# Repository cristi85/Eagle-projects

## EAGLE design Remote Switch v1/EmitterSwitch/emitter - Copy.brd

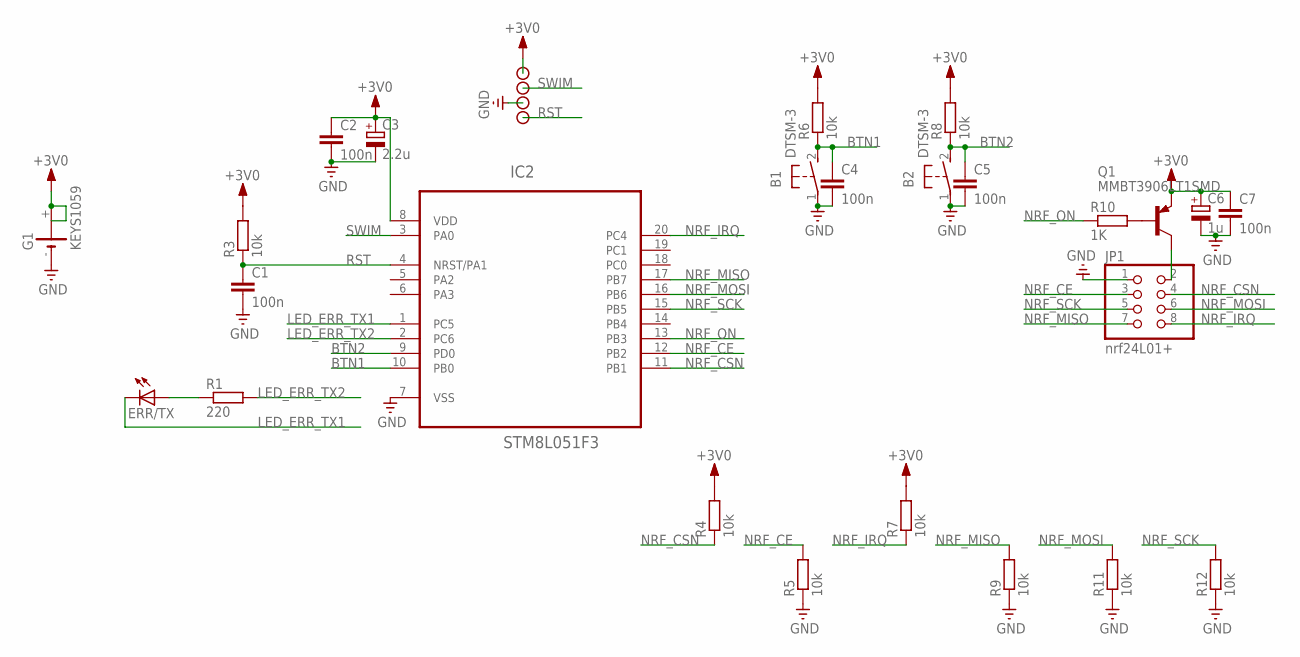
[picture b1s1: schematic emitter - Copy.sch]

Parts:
B1, B2: DTSM-3
C1, C2, C4, C5, C7: 100n; C0603K
C3: 2.2u; SMC_A
C6: 1u; SMC_A
ERR/TX: LED3MM
G1: KEYS1059
IC2: STM8L051F3; TSSOP20
JP1: nrf24L01+; 2X04
Q1: MMBT3906LT1SMD; SOT23-BEC
R1: 220; R0603
R3, R4, R5, R6, R7, R8, R9, R11, R12: 10k; R0603
R10: 1K; R0603
SIG_+3V1: CON_PAD; SMD_PAD
SIG_GND: CON_PAD; SMD_PAD
SIG_RST: CON_PAD; SMD_PAD
SIG_SWIM: CON_PAD; SMD_PAD

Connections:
+3V0: C2.1, C3.+, C6.+, C7.1, G1.+, G1.@+ (+), IC2.8 (VDD), Q1.E, R3.2, R4.2, R6.2, R7.2, R8.2, SIG_+3V1.P$1
BTN1: B1.2, C4.1, IC2.10 (PB0), R6.1
BTN2: B2.2, C5.1, IC2.9 (PD0), R8.1
GND: B1.1, B2.1, C1.2, C2.2, C3.-, C4.2, C5.2, C6.-, C7.2, G1.-, IC2.7 (VSS), JP1.1, R5.1, R9.1, R11.1, R12.1, SIG_GND.P$1
LED_ERR_TX1: ERR/TX.K (C), IC2.1 (PC5)
LED_ERR_TX2: IC2.2 (PC6), R1.2
unnamed: ERR/TX.A, R1.1
unnamed: JP1.2, Q1.C
unnamed: Q1.B, R10.2
NRF_CE: IC2.12 (PB2), JP1.3, R5.2
NRF_CSN: IC2.11 (PB1), JP1.4, R4.1
NRF_IRQ: IC2.20 (PC4), JP1.8, R7.1
NRF_MISO: IC2.17 (PB7), JP1.7, R9.2
NRF_MOSI: IC2.16 (PB6), JP1.6, R11.2
NRF_ON: IC2.13 (PB3), R10.1
NRF_SCK: IC2.15 (PB5), JP1.5, R12.2
RST: C1.1, IC2.4 (NRST/PA1), R3.1, SIG_RST.P$1
SWIM: IC2.3 (PA0), SIG_SWIM.P$1

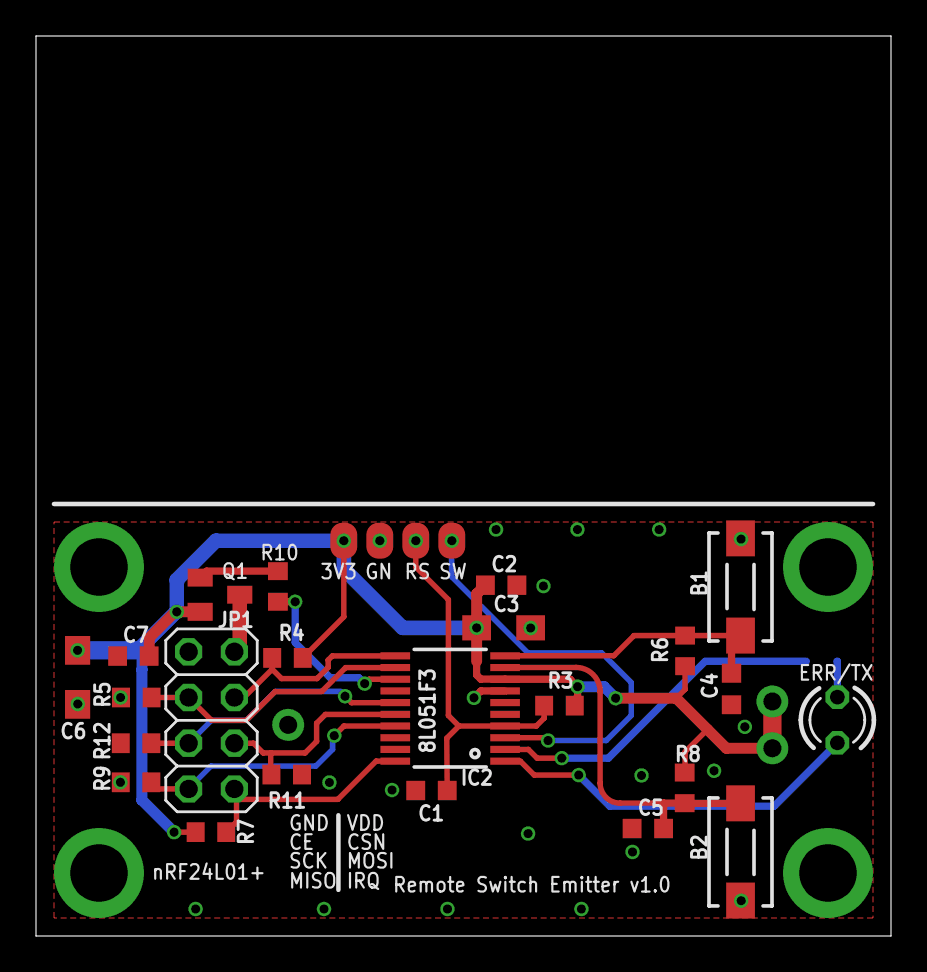
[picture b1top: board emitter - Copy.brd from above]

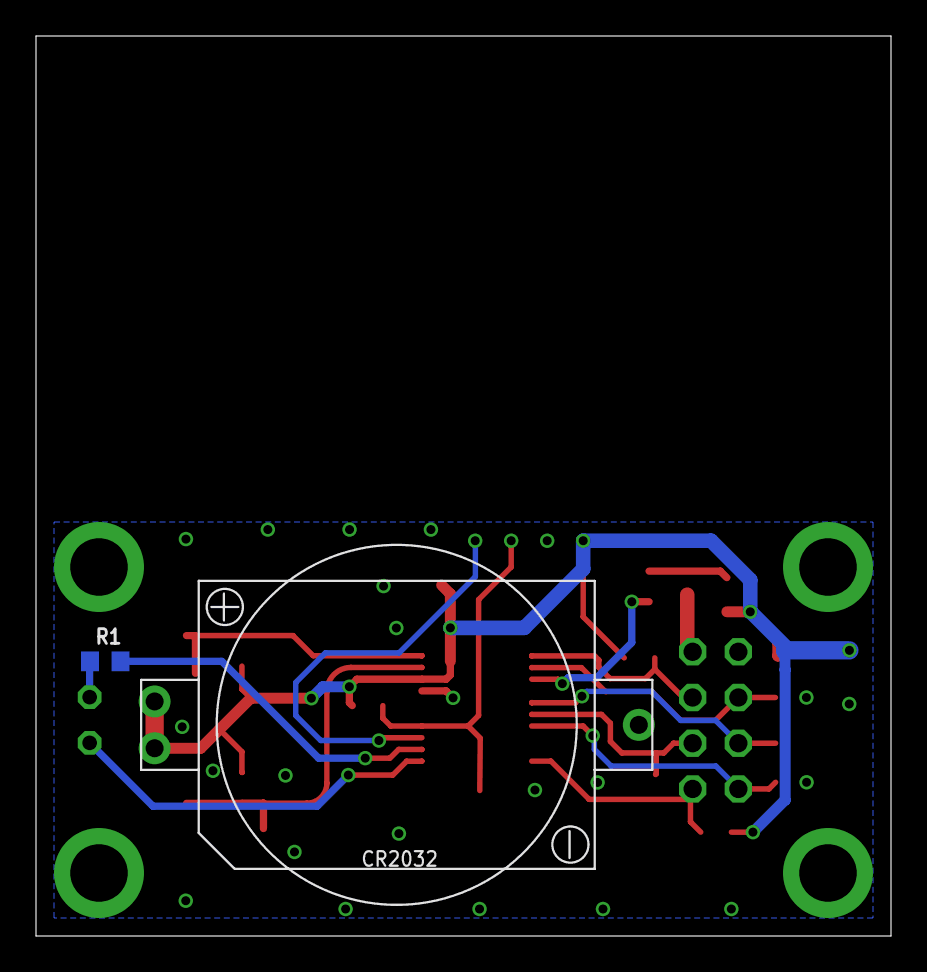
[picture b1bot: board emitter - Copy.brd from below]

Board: 2 copper layers, 47.5 x 50.0 mm, 29 parts (2 on the bottom side), 18 nets.

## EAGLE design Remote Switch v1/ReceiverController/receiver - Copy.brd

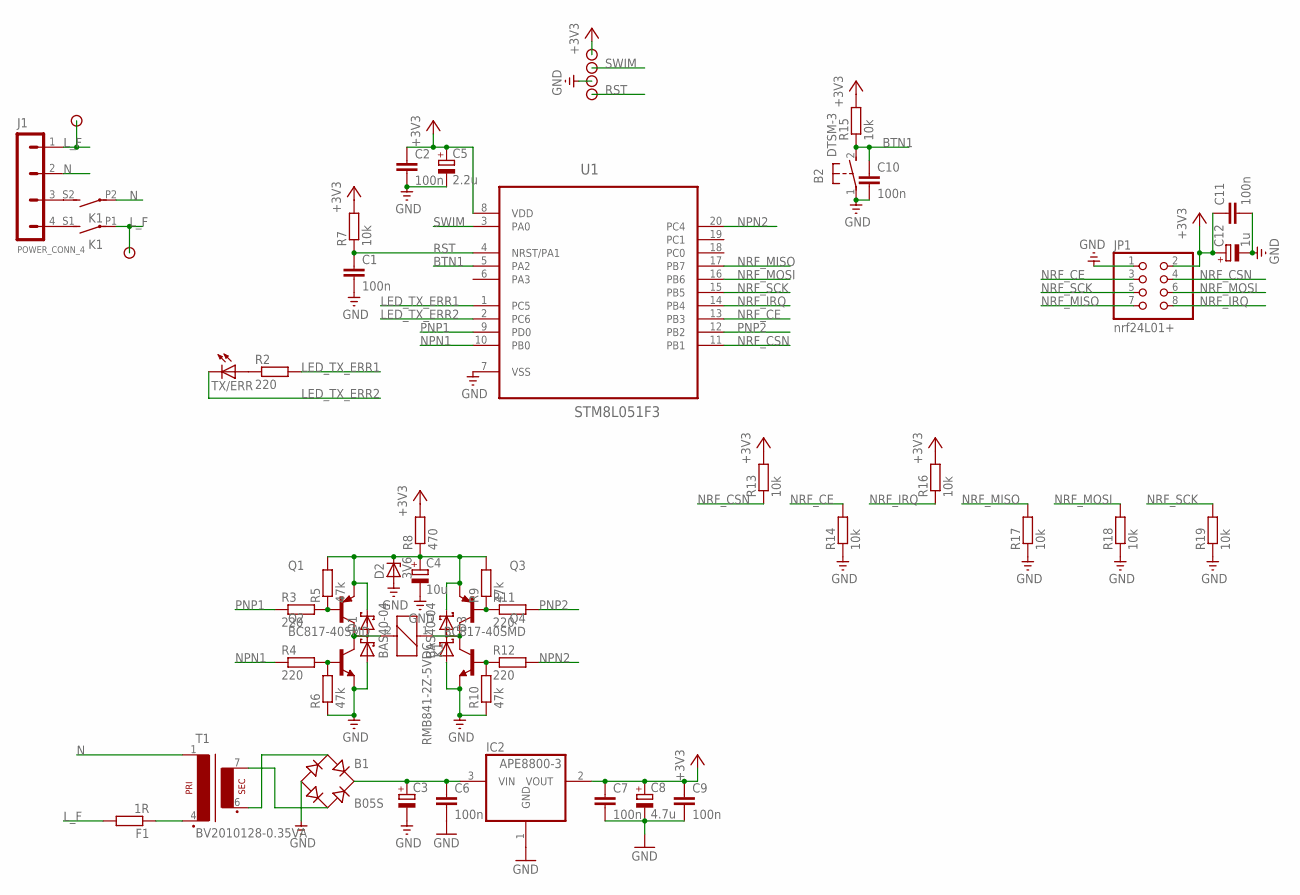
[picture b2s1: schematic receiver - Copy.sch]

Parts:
B1: B05S; MBS
B2: DTSM-3
C1, C2, C6, C7, C9, C10, C11: 100n; C0603K
C3: CPOL-EUSMCB; SMC_B
C4: 10u; SMC_B
C5: 2.2u; SMC_A
C8: 4.7u; SMC_A
C12: 1u; SMC_A
D1, D3: BAS40-04; SOT23
D2: 3V6; SOT23
F1: 1R; 0207/10
IC2: APE8800-3; SOT23
J1: POWER_CONN_4; TERMINAL_BLOCK_4
J2, J3: CON_PAD_THICK_WIRE; SMD_PAD_THICK_WIRE
JP1: nrf24L01+; 2X04
K1: RMB841-2Z-5VDC
Q1, Q3: BC807-40-PNP-SOT23-BEC; SOT23-BEC
Q2, Q4: BC817-40SMD; SOT23-BEC
R2, R3, R4, R11, R12: 220; R0603
R5, R6, R9, R10: 47k; R0603
R7, R13, R14, R15, R16, R17, R18, R19: 10k; R0603
R8: 470; R0603
SIG_+3V1: CON_PAD; SMD_PAD
SIG_GND: CON_PAD; SMD_PAD
SIG_RST: CON_PAD; SMD_PAD
SIG_SWIM: CON_PAD; SMD_PAD
T1: BV2010128-0.35VA
TX/ERR: LED3MM
U1: STM8L051F3; TSSOP20

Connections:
+3V3: C2.1, C5.+, C7.1, C8.+, C9.1, C11.1, C12.+, IC2.2 (VOUT), JP1.2, R7.2, R8.2, R13.2, R15.2, R16.2, SIG_+3V1.P$1, U1.8 (VDD)
BTN1: B2.2, C10.1, R15.1, U1.5 (PA2)
GND: B1.-, B2.1, C1.2, C2.2, C3.-, C4.-, C5.-, C6.2, C7.2, C8.-, C9.2, C10.2, C11.2, C12.-, D1.1 (A1), D2.1 (A), D3.1 (A1), IC2.1 (GND), JP1.1, Q2.E, Q4.E, R6.1, R10.1, R14.1, R17.1, R18.1, R19.1, SIG_GND.P$1, U1.7 (VSS)
LED_TX_ERR1: R2.2, U1.1 (PC5)
LED_TX_ERR2: TX/ERR.K (C), U1.2 (PC6)
L_F: F1.2, J1.1, J2.P$1, J3.P$1, K1.P1
N: J1.2, K1.P2, T1.1
unnamed: R2.1, TX/ERR.A
unnamed: B1.AC2, T1.7 (S4)
unnamed: B1.+, C3.+, C6.1, IC2.3 (VIN)
unnamed: B1.AC1, T1.6 (S3)
unnamed: Q2.B, R4.2, R6.2
unnamed: D1.3 (C1A2), K1.2, Q1.C, Q2.C
unnamed: Q4.B, R10.2, R12.1
unnamed: Q1.B, R3.2, R5.1
unnamed: Q3.B, R9.1, R11.1
unnamed: J1.4, K1.S1 (S)
unnamed: J1.3, K1.S2 (S)
unnamed: D3.3 (C1A2), K1.1, Q3.C, Q4.C
unnamed: C4.+, D1.2 (C2), D2.3 (C), D3.2 (C2), Q1.E, Q3.E, R5.2, R8.1, R9.2
unnamed: F1.1, T1.4 (P2)
NPN1: R4.1, U1.10 (PB0)
NPN2: R12.2, U1.20 (PC4)
NRF_CE: JP1.3, R14.2, U1.13 (PB3)
NRF_CSN: JP1.4, R13.1, U1.11 (PB1)
NRF_IRQ: JP1.8, R16.1, U1.14 (PB4)
NRF_MISO: JP1.7, R17.2, U1.17 (PB7)
NRF_MOSI: JP1.6, R18.2, U1.16 (PB6)
NRF_SCK: JP1.5, R19.2, U1.15 (PB5)
PNP1: R3.1, U1.9 (PD0)
PNP2: R11.2, U1.12 (PB2)
RST: C1.1, R7.1, SIG_RST.P$1, U1.4 (NRST/PA1)
SWIM: SIG_SWIM.P$1, U1.3 (PA0)

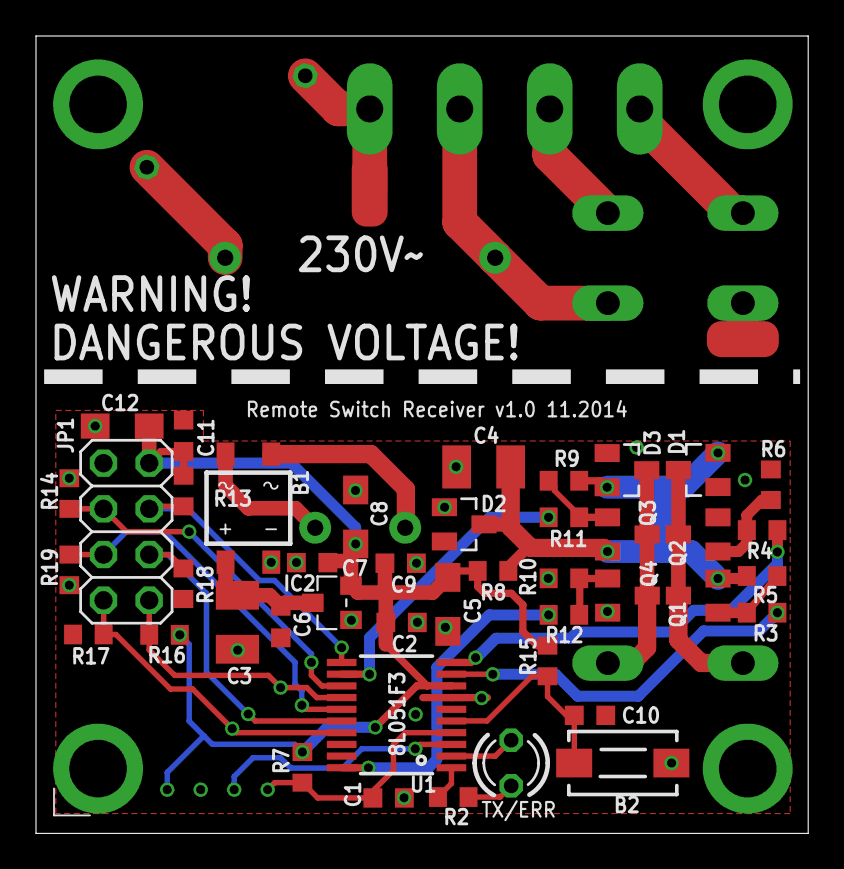
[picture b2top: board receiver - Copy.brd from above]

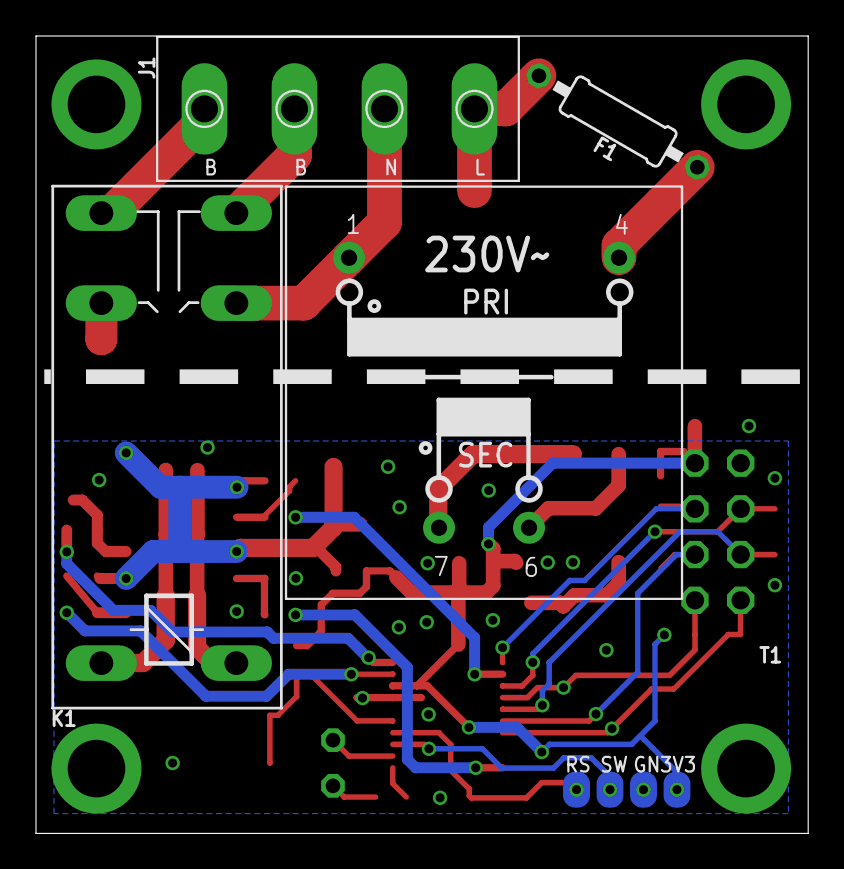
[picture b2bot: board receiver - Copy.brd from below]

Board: 2 copper layers, 42.9 x 44.3 mm, 53 parts (8 on the bottom side), 33 nets.

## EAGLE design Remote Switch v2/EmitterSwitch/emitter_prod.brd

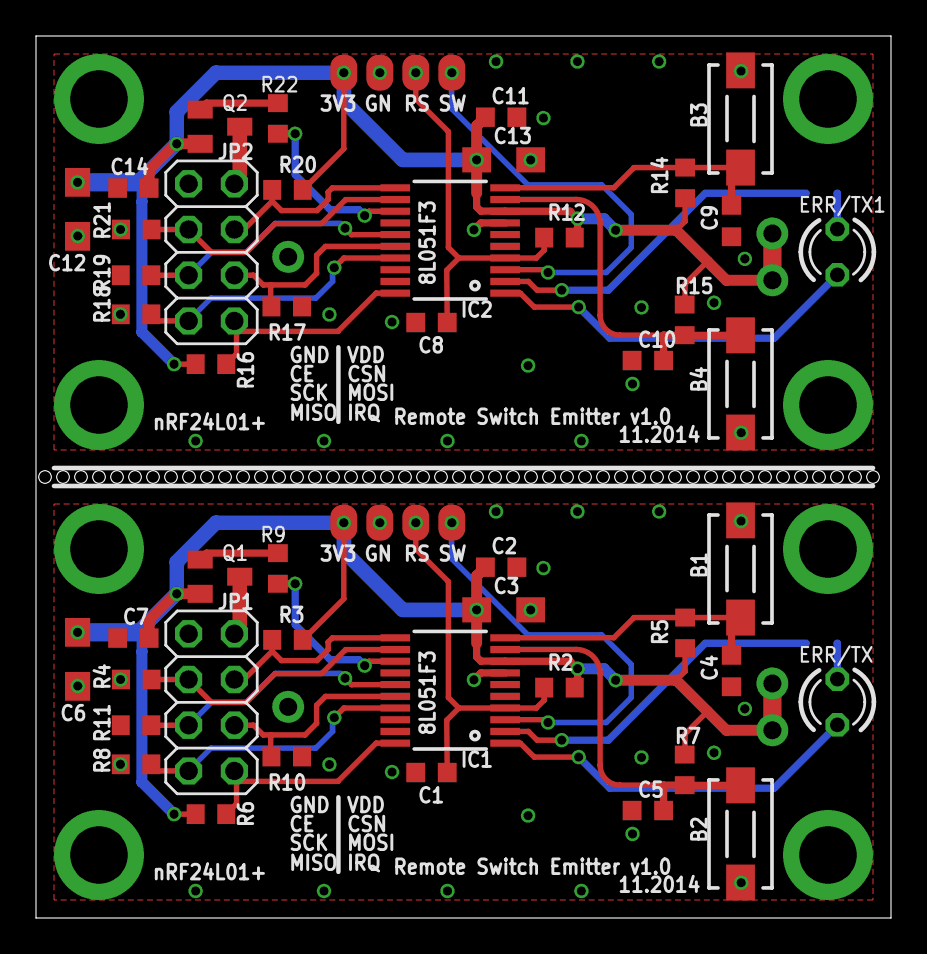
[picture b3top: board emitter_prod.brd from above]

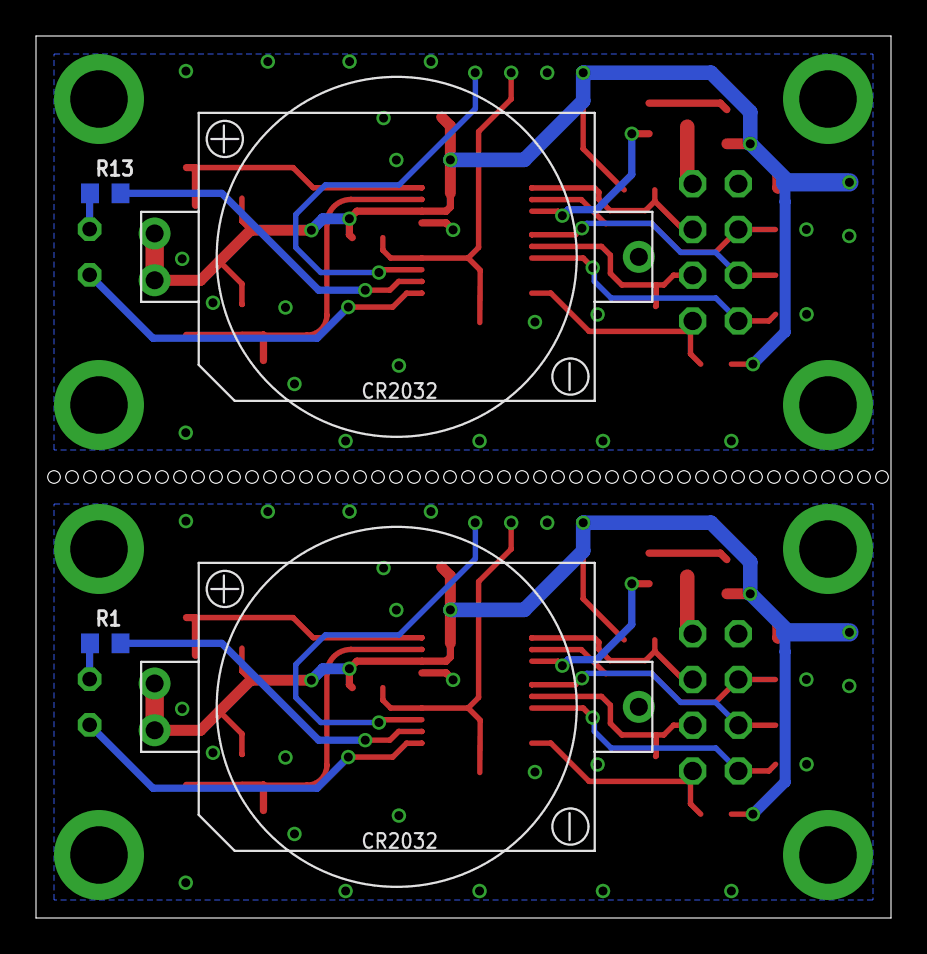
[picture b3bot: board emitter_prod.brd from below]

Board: 2 copper layers, 47.5 x 49.0 mm, 58 parts (4 on the bottom side), 36 nets.

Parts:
B1, B2, B3, B4: DTSM-3
C1, C2, C4, C5, C7, C8, C9, C10, C11, C14: 100n; C0603K
C3, C13: 2.2u; SMC_A
C6, C12: 1u; SMC_A
ERR/TX, ERR/TX1: LED3MM
G1, G2: KEYS1059
IC1, IC2: STM8L051F3; TSSOP20
JP1, JP2: nrf24L01+; 2X04
Q1, Q2: MMBT3906LT1SMD; SOT23-BEC
R1, R13: 220; R0603
R2, R3, R4, R5, R6, R7, R8, R10, R11, R12, R14, R15, R16, R17, R18, R19, R20, R21: 10k; R0603
R9, R22: 1K; R0603
SIG_+3V1, SIG_+3V2: CON_PAD; SMD_PAD
SIG_GND, SIG_GND1: CON_PAD; SMD_PAD
SIG_RST, SIG_RST1: CON_PAD; SMD_PAD
SIG_SWIM, SIG_SWIM1: CON_PAD; SMD_PAD

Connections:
+3V0: C2.1, C3.+, C6.+, C7.1, G1.+, G1.@+, IC1.8, Q1.E, R2.2, R3.2, R5.2, R6.2, R7.2, SIG_+3V1.P$1
+3V1: C11.1, C12.+, C13.+, C14.1, G2.+, G2.@+, IC2.8, Q2.E, R12.2, R14.2, R15.2, R16.2, R20.2, SIG_+3V2.P$1
BTN1: B1.2, C4.1, IC1.10, R5.1
BTN2: B2.2, C5.1, IC1.9, R7.1
BTN3: B3.2, C9.1, IC2.10, R14.1
BTN4: B4.2, C10.1, IC2.9, R15.1
GND: B1.1, B2.1, C1.2, C2.2, C3.-, C4.2, C5.2, C6.-, C7.2, G1.-, IC1.7, JP1.1, R4.1, R8.1, R10.1, R11.1, SIG_GND.P$1
GND1: B3.1, B4.1, C8.2, C9.2, C10.2, C11.2, C12.-, C13.-, C14.2, G2.-, IC2.7, JP2.1, R17.1, R18.1, R19.1, R21.1, SIG_GND1.P$1
LED_ERR_TX1: ERR/TX.K, IC1.1
LED_ERR_TX2: IC1.2, R1.2
LED_ERR_TX3: IC2.2, R13.2
LED_ERR_TX4: ERR/TX1.K, IC2.1
unnamed: ERR/TX.A, R1.1
unnamed: JP1.2, Q1.C
unnamed: Q1.B, R9.2
unnamed: JP2.2, Q2.C
unnamed: Q2.B, R22.2
unnamed: ERR/TX1.A, R13.1
NRF_CE: IC1.12, JP1.3, R4.2
NRF_CE1: IC2.12, JP2.3, R21.2
NRF_CSN: IC1.11, JP1.4, R3.1
NRF_CSN1: IC2.11, JP2.4, R20.1
NRF_IRQ: IC1.20, JP1.8, R6.1
NRF_IRQ1: IC2.20, JP2.8, R16.1
NRF_MISO: IC1.17, JP1.7, R8.2
NRF_MISO1: IC2.17, JP2.7, R18.2
NRF_MOSI: IC1.16, JP1.6, R10.2
NRF_MOSI1: IC2.16, JP2.6, R17.2
NRF_ON: IC1.13, R9.1
NRF_ON1: IC2.13, R22.1
NRF_SCK: IC1.15, JP1.5, R11.2
NRF_SCK1: IC2.15, JP2.5, R19.2
RST: C1.1, IC1.4, R2.1, SIG_RST.P$1
RST1: C8.1, IC2.4, R12.1, SIG_RST1.P$1
SWIM: IC1.3, SIG_SWIM.P$1
SWIM1: IC2.3, SIG_SWIM1.P$1

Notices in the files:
parts and their libraries:
supply1: Copyright (C) 2007, Bob Starr
